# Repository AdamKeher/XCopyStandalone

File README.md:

# XCopy Standalone
An Arduino / Teensy based version of the Amiga XCopy application for copying floppy disks to and from ADF files. Built for the Teensy 3.2 using a custom PCB and an unmodified PC 3.5" floppy disk drive.

### Note
XCopy Standalone liberally uses floppy interface code taken from the excelent and generously open source ADF-Copy by Dominik Tonn. 
https://nickslabor.niteto.de/download/
Nicks software uses usb serial and a Java client or a MTP connection via usb to transfer data. XCopy Standalone focuses on a standalone unit using SD card storage and a LCD and / or web sockets interface for control.

### Thanks
Special thanks to Giants for all his help with this version including web interface graphics, documentation, suggestions etc.

## Device

## Status
This project is under heavy development and is in a state of flux with new hardware and software being actively worked on. The firmware version lives in `src/XCopy/XCopy.h`; this README describes v743.26.

## New Features - 09/2026

Since the 04/2023 release the device has grown a flux layer under the copier, a
second file system layer over the SD card, and a rebuilt web interface.

* **Disk Info** - a track analyser that describes what is on a disk rather than
  copying it. One pass per track, no retries, so a protected track with the wrong
  cylinder in its headers, a track with no sectors at all, or a disk with 84
  cylinders instead of 80 is the output rather than an error. Draws both surfaces
  as disks, a flux interval histogram per track, an angular track view you can
  point at, and the decoded sector under the pointer. Runs against the drive, or
  replays an SCP image through the same decoder.
* **Drive Toolkit** - a bench instrument for bringing up an unknown drive. Every
  interface line sampled with state, counts and rates; the safe outputs drivable
  one at a time, so a drive can be provoked into saying which fault it has; and a
  continuous head calibration read, after Amiga Test Kit's, that reports how many
  of the eleven sectors came back clean and whether the ones that did not came
  from the cylinder either side. Write data and write enable are deliberately not
  exposed.
* **SuperCard Pro flux images** - `readscp` captures a disk to an SCP file,
  streamed a block at a time because a single DD revolution is larger than the RAM
  on the whole part. A matching reader replays one back through the analyser.
* **Live USB flux streaming** - `live` hands the USB session to a host that does
  its own decoding, with non blocking in band seeking so the capture ring is still
  draining during a head move. Host side probe in `files/Tools/xcopylive_probe.py`.
* **ADF images as volumes** - mount ADF files as `ADF0:` and `ADF1:`, and the disk
  in the drive itself as `DF0:`, then use `dir`, `cat`, `cp`, `mkdir` and `rm`
  across the card and any mounted image. Mounts are read only unless asked
  otherwise. ADFlib upgraded to 0.10.7, with drivers rather than local edits.
* **New serial console** - a table driven interpreter with grouped help, per
  command options, tab completion and history, in place of the hand written parser.
* **Rebuilt web interface** - six tabs over one set of shared tokens and
  components, with the Disk Monitor histogram and the Disk Info analysis streamed
  to the browser as they are produced rather than gathered first.
* **Over the air updates** - firmware and web assets over Wi-Fi, no cable needed.
* **A name on the network** - the device calls itself `xcopy` to DHCP, to mDNS and
  to OTA.
* **Host side tests** - the `native` and `native_adf` environments run the file
  system and console tests off the board.

## New Features - 04/2023
* v0.19 PCB released with intergrated ESP8266 for WiFi
  * Moved to Kicad from Eagle
  * Changed SD Card to MicroSD reader
  * Added WiFi
  * Connected USB serial to Teensy USB serial
  * Moved TFT to cheap chinese Adafruit knock off, this has changed the pinout
    * https://www.aliexpress.com/item/4001144194129.html
    * USD $1.89!
  * Moved navigation stick to cheap chinese item from LCSC
  * Additional 3.3v power regulator to relieve Teensy's
  * Added larger electrolytic cap for floppy power
  * Switced to four layer board as they are cheap and provide better power / ground planes
* Project code moved from Arduino to ProjectIO with all libraries preinstalled
* New web interface
* Amiga module ripper
* Bootblock library / virus checker using brainfile format
* Web based disk monitor
* Network NTP time update
* Upload and download ADF files via web interface

## Features
* Software
  * Disk copy
    * Disk to SD Card
    * SD Card to Disk
    * Disk to Disk
    * Disk to Temporary Flash
    * Temporary Flash to Disk
  * Flux
    * Read a disk to a SuperCard Pro (SCP) flux image
    * Analyse a disk, or an SCP image, track by track
    * Flux interval histograms, per track and live during a copy
    * Stream a live drive to a host over USB for off board decoding
  * File systems
    * Amiga file system support for floppy disks and ADF files via ADFlib 0.10.7
    * Mount ADF images as `ADF0:` / `ADF1:`, and the disk in the drive as `DF0:`
    * List, print, copy, make and remove across the card and mounted images
  * Drive diagnostics
    * Every interface line sampled, with state, counts and rates
    * Individually drivable outputs for provoking a fault out of a drive
    * Continuous head calibration read with a live per cylinder tally
    * Drive speed from the index
  * Test disk
  * Format disk
  * Search a disk for case sensitive ascii text, or for tracker modules
  * Amiga module ripper
  * Bootblock library / virus checker using brainfile format
  * Serial command line, table driven, with tab completion and history
  * Interfaces
    * TFT LCD
    * USB Serial
    * HTML over WebSockets
  * Network
    * Over the air firmware and web asset updates
    * NTP time update and time zone
    * Announces itself as `xcopy` to DHCP, mDNS and OTA
  * Serial passthrough for programming onboard ESP8266
* Hardware
  * IDC 34 pin standard floppy drive cable interface
  * 1.8" ST7735R 128x160, 18bit color LCD
  * 5 way navigation joystick
  * Mono PAM8302 amplifier with adjustable Pot
    * Onboard mounted speaker
  * SD Card reader
  * 128MBit Flash Rom with built in ADF files
  * CR1220 battery backed realtime clock
  * ESP8266 for websockets driven interface
  * Single USB plug for serial and to power floppy and Teensy 3.2
  * Status LED's
  * Additional 3.3v power regulator
  * Gerbers, schematic and pcb layout files available 

# PCB

# Web Interface

Six tabs over one WebSocket connection to the ESP8266. The footer carries the
signal strength, the link state and what the device is doing, on every tab.

### Disk Copy

Every copy path in one place - between the drive, the SD card, the onboard flash,
and an ADF or SCP file on the card - over a live track map of both surfaces and a
rolling flux view of the track being read.

### Disk Monitor

A sector at a time: the decoded header, a hex dump, an ascii dump in either the
browser font or the Amiga one, and the track's flux histogram. Below them a block
scan of the whole disk, with ascii and tracker module searches, and blocks that
can be selected and written out to the card.

### Disk Info

The analyser. Both surfaces drawn as disks with every sector coloured by what was
found there, a status panel for the selected track, an angular track view of the
raw cell stream against the sectors decoded out of it, the flux histogram, and the
decoded sector under the pointer.

### Drive Toolkit

The drive itself rather than the disk in it. Sampled interface lines down the
left, the calibration read across the top, and a session tally that accumulates
per cylinder and head - so an intermittent read shows up as intermittent rather
than as one bad pass.

### SD Card

The contents of the card, with upload and download.

### Log

The serial console in the browser - the same interpreter, the same commands and
the same output as the USB port.

# Build Environment Notes:

## VSCode Plugins:
1. PlatoformIO with Teensy & ESP8266 board 
2. Todo+ v4.18.4 by Fabio Spampinato

* Xcopy.h contains PCBVERSION define to target firmware builds to different PCB versions

## ESP8266 Build Notes:
1. Select the `d1_mini` environment (both boards are environments of this one project)
2. Plugin XCopyStandalone device and select "Debugging >> ESP >> ESP Programming Mode"
3. Set serial port to the Teensy port, the device will passthrough serial data to the ESP8266 program
4. Upload code, then upload the web assets with the `d1_mini` "Build Filesystem Image" and "Upload Filesystem Image" tasks

### Over the air

Once the ESP is on your network it can be updated over Wi-Fi instead, using the
`d1_mini_ota` environment - both the firmware and the web assets:

```shell
pio run -e d1_mini_ota -t upload      # firmware
pio run -e d1_mini_ota -t uploadfs    # web interface
pio run -e d1_mini_ota -t uploadall   # both, firmware first
```

`uploadall` is a task of this project rather than of PlatformIO, and it waits
between the two because each upload reboots the ESP.

Use `uploadfs` for the web assets, not `uploadfsota`. The platform decides
whether espota is offering a sketch or a filesystem image by matching the target
name exactly, and `uploadfsota` misses that test - so the image goes over as a
sketch, is measured against the 1MB sketch region instead of its own 2MB
partition, and is refused with `ERROR[4]: Not Enough Space`. `scripts/
espota_fs_flag.py` puts the missing flag back, so both targets now work.

The device calls itself `xcopy` to the DHCP server, to mDNS and to OTA, so it is
reachable by whichever name your network gives it. `upload_port` in
`platformio.ini` is set to `xcopy.lab` - change it to `xcopy.local` to go via
mDNS instead, or to a bare IP address if neither resolves from your machine.

The serial passthrough above is unchanged and remains the way back in if an
update ever leaves the ESP unable to join a network.
5. Select "Debugging >> ESP >> Reset ESP"
6. Open a serial terminal
7. Connect to your wireless access point using the connect command
```shell
>> connect SSIDName Password
```
8. Type the following commands to confirm you have connected
```shell
>> status
WiFi Status: Connected
-----
Mode: STA
PHY mode: N
Channel: 10
AP id: 0
Status: 5
Auto connect: 1
SSID (6): SSIDName
Passphrase (12): Password
BSSID set: 0
>> ip
192.168.X.XX
>> ssid
SSIDName
>>
```

## Project layout

Both firmwares are environments of a single PlatformIO project, so the IDE lists
them in one Project Tasks tree and `pio run` with no arguments builds the pair.

| | |
|---|---|
| `src/` | Teensy 3.2 firmware, built by the `teensy31` environment |
| `src/esp8266/` | ESP8266 firmware, built by the `d1_mini` environment |
| `esp8266/data/` | web interface, uploaded to the ESP as a LittleFS image |
| `shared/` | the Teensy to ESP link contract, compiled into both |
| `lib/` | libraries for both; `esp8266/lib/` holds the ESP only ones |

Both boards are environments of the one project: `teensy31`, `d1_mini`, and
`d1_mini_ota` for updating the ESP over Wi-Fi. Two more, `native` and
`native_adf`, build nothing for a board and exist to run the console and file
system tests on the host.

Neither firmware is a `.ino` sketch: PlatformIO only converts a sketch sitting at
the top of the source directory, and with two source trees neither one can be.

## How to build PlatformIO based project

1. [Install PlatformIO Core](http://docs.platformio.org/page/core.html)
2. Download [development platform with examples](https://github.com/platformio/platform-teensy/archive/develop.zip)
3. Open the project
4. Pick the environment you want - `teensy31` or `d1_mini` - or build both at once
5. Select 'PlatformIO:Build'
6. Select 'PlatformIO:Upload'

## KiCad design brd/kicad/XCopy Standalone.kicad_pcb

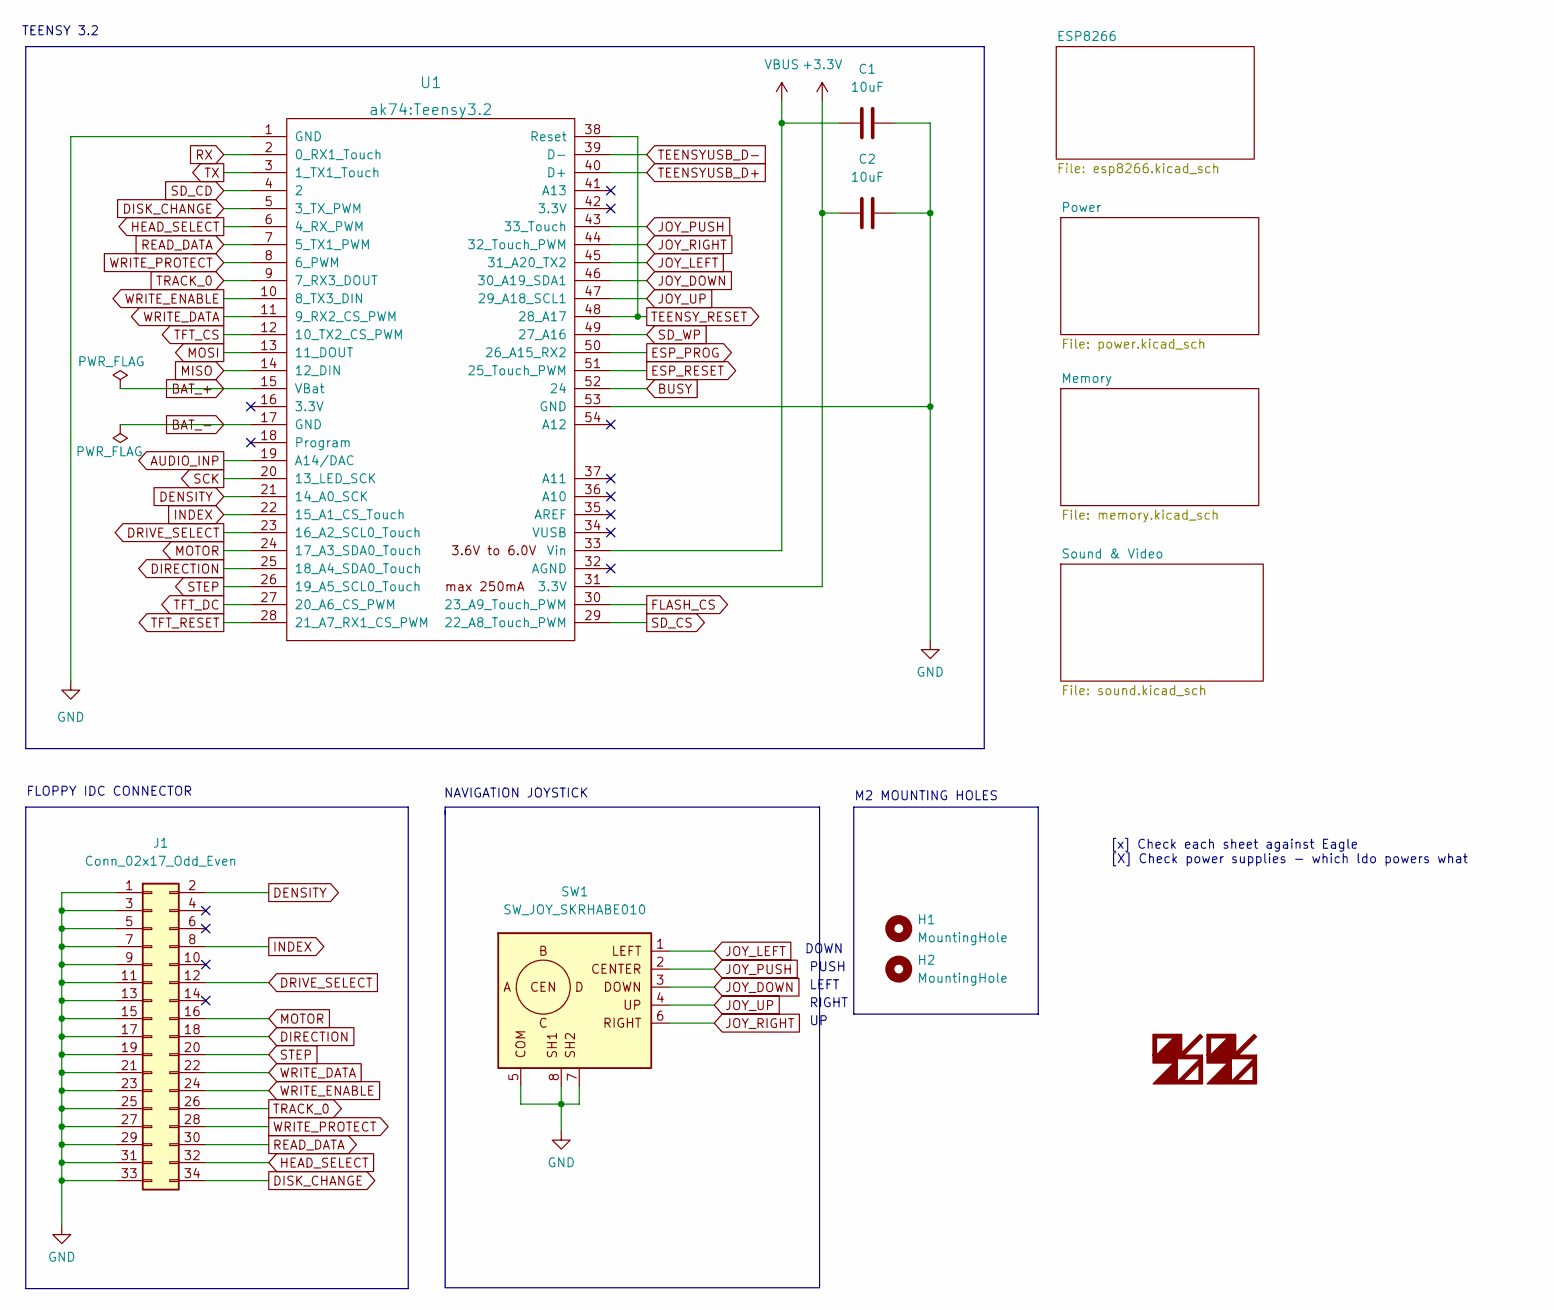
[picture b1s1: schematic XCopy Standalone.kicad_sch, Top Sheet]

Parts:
C1, C2: 10uF; C_0603_1608Metric_Pad1.08x0.95mm_HandSolder
H1, H2: MountingHole; MountingHole_2.2mm_M2
J1: Conn_02x17_Odd_Even; IDC-Header_2x17_P2.54mm_Horizontal_FLOPPY
SW1: SW_JOY_SKRHABE010; Switches_ALPS-SKRHAAE010; LCSC C139794
U1: ak74:Teensy3.2; Teensy30_31_32_All_Pins

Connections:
+3.3V: C2.2, U1.31 (3.3V); also elsewhere on the board
AUDIO_INP: U1.19 (A14/DAC); also elsewhere on the board
BAT_+: U1.15 (VBat); also elsewhere on the board
BAT_-: U1.17 (GND); also elsewhere on the board
BUSY: U1.52 (24); also elsewhere on the board
DENSITY: J1.2, U1.21 (14_A0_SCK)
DIRECTION: J1.18, U1.25 (18_A4_SDA0_Touch)
DISK_CHANGE: J1.34, U1.5 (3_TX_PWM)
DRIVE_SELECT: J1.12, U1.23 (16_A2_SCL0_Touch)
ESP_PROG: U1.50 (26_A15_RX2); also elsewhere on the board
ESP_RESET: U1.51 (25_Touch_PWM); also elsewhere on the board
FLASH_CS: U1.30 (23_A9_Touch_PWM); also elsewhere on the board
GND: C1.1, C2.1, J1.1, J1.3, J1.5, J1.7, J1.9, J1.11, J1.13, J1.15, J1.17, J1.19, J1.21, J1.23, J1.25, J1.27, J1.29, J1.31, J1.33, SW1.5 (COM), SW1.7 (SH2), SW1.8 (SH1), U1.1 (GND), U1.53 (GND); also elsewhere on the board
HEAD_SELECT: J1.32, U1.6 (4_RX_PWM)
INDEX: J1.8, U1.22 (15_A1_CS_Touch)
JOY_DOWN: SW1.3 (C), U1.46 (30_A19_SDA1)
JOY_LEFT: SW1.1 (A), U1.45 (31_A20_TX2); also elsewhere on the board
JOY_PUSH: SW1.2 (Center), U1.43 (33_Touch)
JOY_RIGHT: SW1.6 (D), U1.44 (32_Touch_PWM)
JOY_UP: SW1.4 (B), U1.47 (29_A18_SCL1)
MISO: U1.14 (12_DIN); also elsewhere on the board
MOSI: U1.13 (11_DOUT); also elsewhere on the board
MOTOR: J1.16, U1.24 (17_A3_SDA0_Touch)
READ_DATA: J1.30, U1.7 (5_TX1_PWM)
RX: U1.2 (0_RX1_Touch); also elsewhere on the board
SCK: U1.20 (13_LED_SCK); also elsewhere on the board
SD_CD: U1.4 (2); also elsewhere on the board
SD_CS: U1.29 (22_A8_Touch_PWM); also elsewhere on the board
SD_WP: U1.49 (27_A16); also elsewhere on the board
STEP: J1.20, U1.26 (19_A5_SCL0_Touch)
TEENSYUSB_D+: U1.40 (D+); also elsewhere on the board
TEENSYUSB_D-: U1.39 (D-); also elsewhere on the board
TEENSY_RESET: U1.38 (Reset), U1.48 (28_A17); also elsewhere on the board
TFT_CS: U1.12 (10_TX2_CS_PWM); also elsewhere on the board
TFT_DC: U1.27 (20_A6_CS_PWM); also elsewhere on the board
TFT_RESET: U1.28 (21_A7_RX1_CS_PWM); also elsewhere on the board
TRACK_0: J1.26, U1.9 (7_RX3_DOUT)
TX: U1.3 (1_TX1_Touch); also elsewhere on the board
VBUS: C1.2, U1.33 (Vin); also elsewhere on the board
WRITE_DATA: J1.22, U1.11 (9_RX2_CS_PWM)
WRITE_ENABLE: J1.24, U1.10 (8_TX3_DIN)
WRITE_PROTECT: J1.28, U1.8 (6_PWM)

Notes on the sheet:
DOWN
NAVIGATION JOYSTICK
TEENSY 3.2
[x] Check each sheet against Eagle [X] Check power supplies - which ldo powers what
M2 MOUNTING HOLES
FLOPPY IDC CONNECTOR
LEFT
RIGHT
PUSH

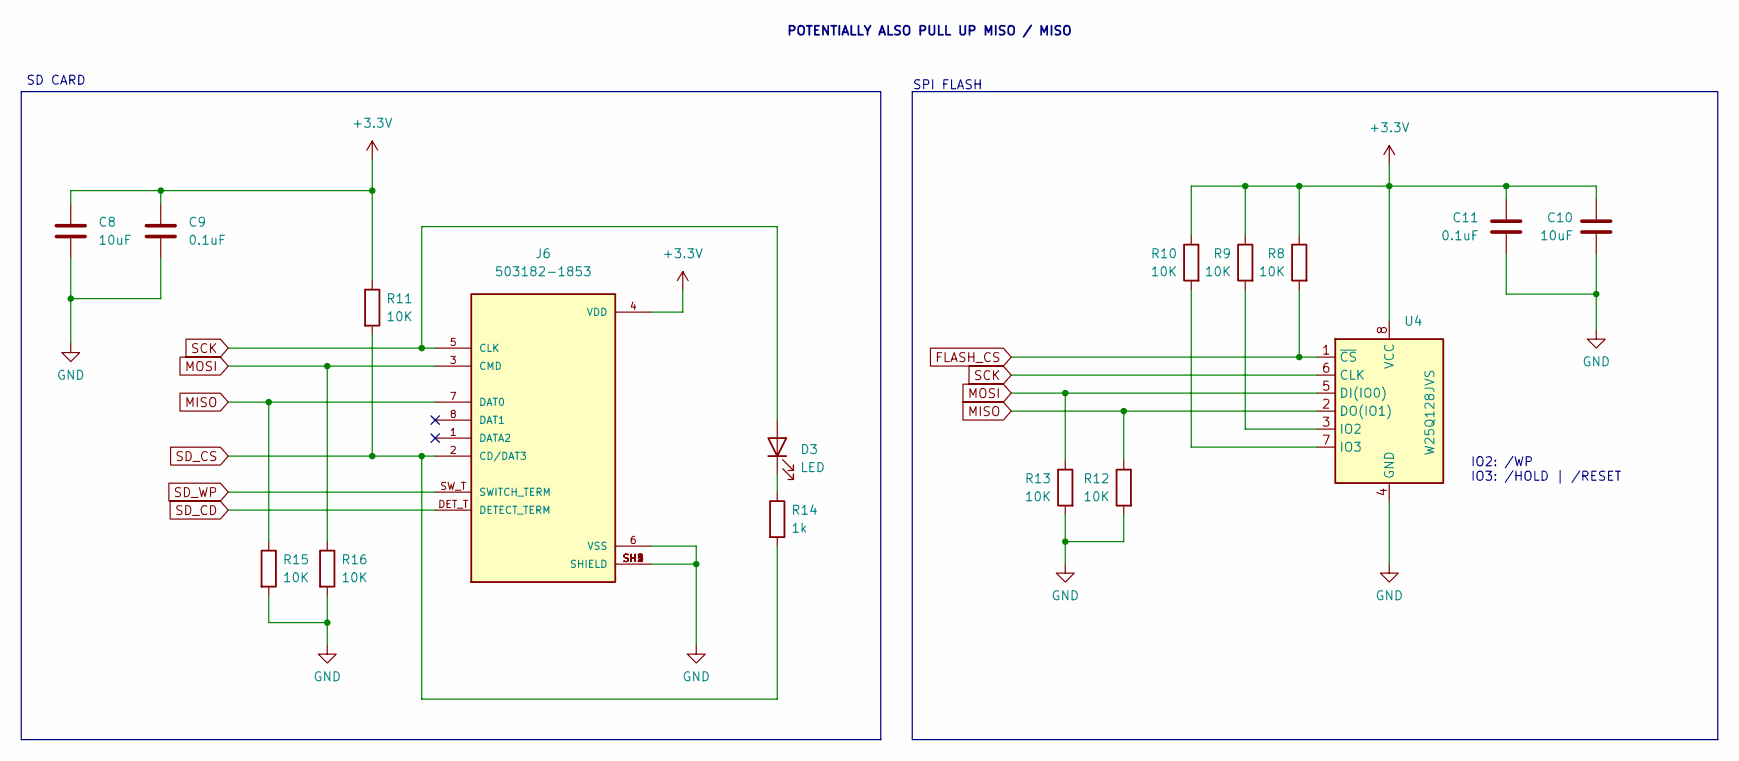
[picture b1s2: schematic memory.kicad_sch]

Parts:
C8, C10: 10uF; C_0603_1608Metric_Pad1.08x0.95mm_HandSolder
C9, C11: 0.1uF; C_0603_1608Metric_Pad1.08x0.95mm_HandSolder
D3: LED; LED_0603_1608Metric_Pad1.05x0.95mm_HandSolder
J6: 503182-1853; MOLEX_503182-1853-2; PARTREV G; LCSC C266617
R8, R9, R10, R11, R12, R13, R15, R16: 10K; R_0603_1608Metric_Pad0.98x0.95mm_HandSolder
R14: 1k; R_0603_1608Metric_Pad0.98x0.95mm_HandSolder
U4: W25Q128JVS; SOIC-8_5.23x5.23mm_P1.27mm; LCSC C571265

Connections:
+3.3V: C8.1, C9.1, C10.1, C11.1, J6.4 (VDD), R8.1, R9.1, R10.1, R11.1, U4.8 (VCC); also elsewhere on the board
FLASH_CS: R8.2, U4.1 (~CS); also elsewhere on the board
GND: C8.2, C9.2, C10.2, C11.2, J6.6 (VSS), J6.SH1 (SHIELD), J6.SH2 (SHIELD), J6.SH3 (SHIELD), J6.SH4 (SHIELD), J6.SH5 (SHIELD), R12.2, R13.2, R15.2, R16.2, U4.4 (GND); also elsewhere on the board
MISO: J6.7 (DAT0), R12.1, R15.1, U4.2 (DO(IO1)); also elsewhere on the board
MOSI: J6.3 (CMD), R13.1, R16.1, U4.5 (DI(IO0)); also elsewhere on the board
unnamed: D3.1 (K), R14.1
unnamed: R9.2, U4.3 (IO2)
unnamed: R10.2, U4.7 (IO3)
SCK: D3.2 (A), J6.5 (CLK), U4.6 (CLK); also elsewhere on the board
SD_CD: J6.DET_T (DETECT_TERM); also elsewhere on the board
SD_CS: J6.2 (CD/DAT3), R11.2, R14.2; also elsewhere on the board
SD_WP: J6.SW_T (SWITCH_TERM); also elsewhere on the board

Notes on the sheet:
SD CARD
IO2: /WP IO3: /HOLD | /RESET
POTENTIALLY ALSO PULL UP MISO / MISO
SPI FLASH

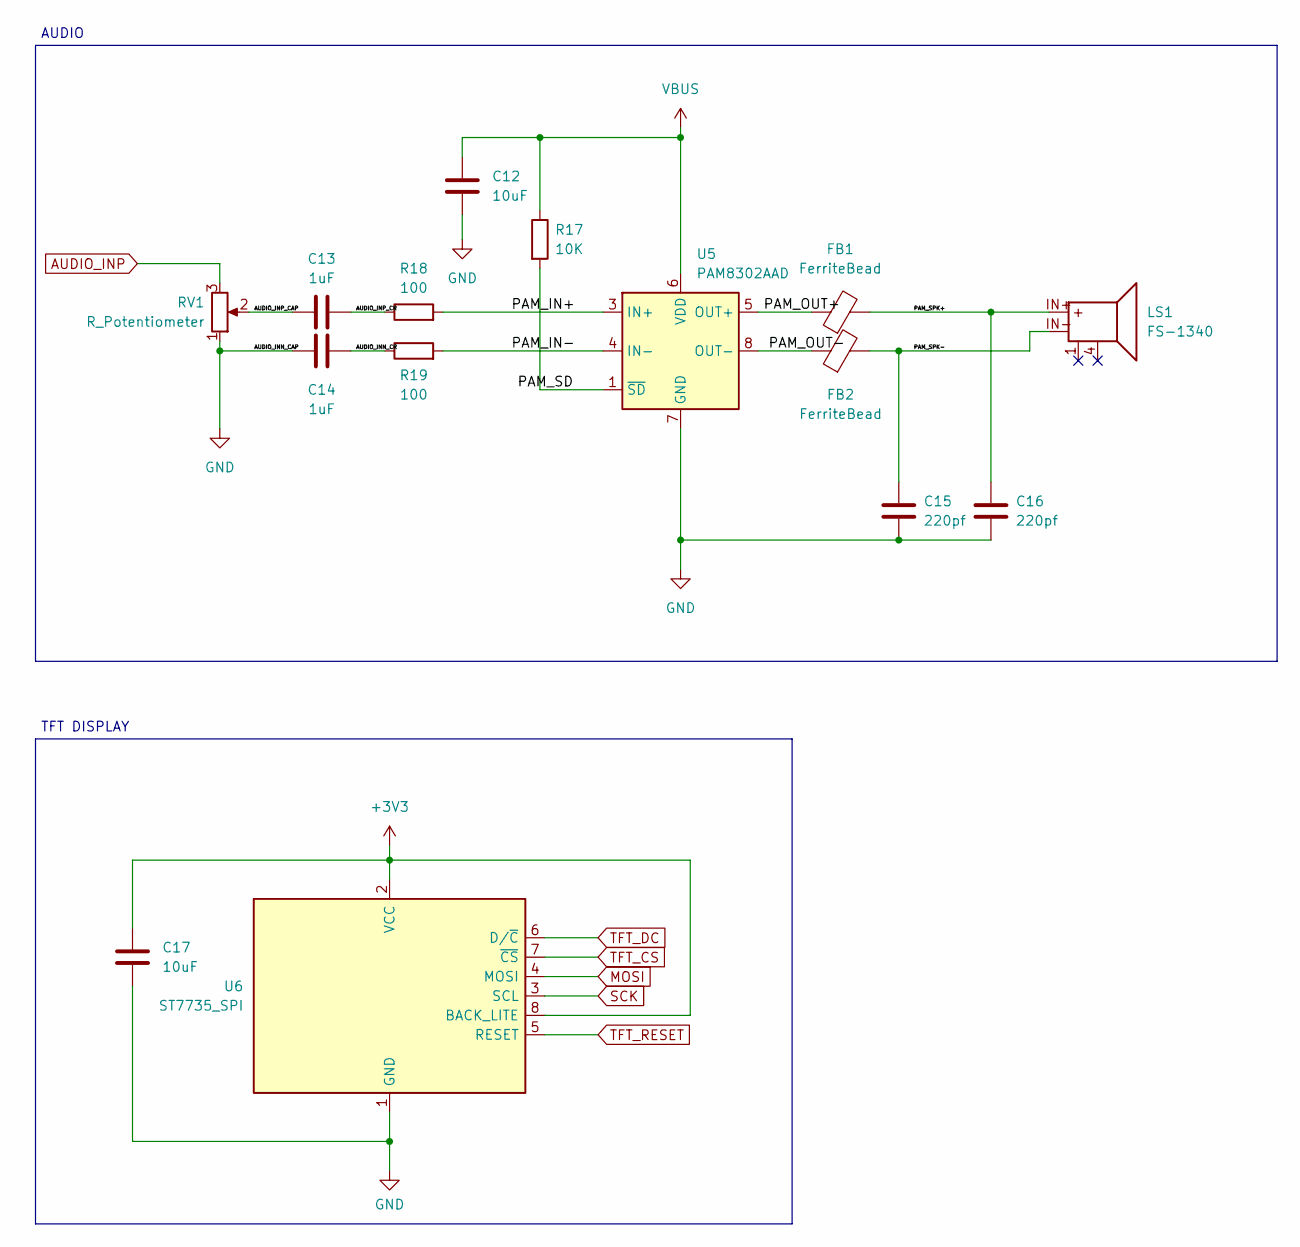
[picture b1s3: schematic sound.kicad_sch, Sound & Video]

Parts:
C12, C17: 10uF; C_0603_1608Metric_Pad1.08x0.95mm_HandSolder
C13, C14: 1uF; C_0603_1608Metric_Pad1.08x0.95mm_HandSolder
C15, C16: 220pf; C_0603_1608Metric_Pad1.08x0.95mm_HandSolder
FB1, FB2: FerriteBead; R_0805_2012Metric_Pad1.20x1.40mm_HandSolder
LS1: FS-1340; SPK_FUET_FS-1340; LCSC C482342
R17: 10K; R_0603_1608Metric_Pad0.98x0.95mm_HandSolder
R18, R19: 100; R_0603_1608Metric_Pad0.98x0.95mm_HandSolder
RV1: R_Potentiometer; Potentiometer_Bourns_TC33X-2; LCSC C719176
U5: PAM8302AAD; SOP-8_3.9x4.9mm_P1.27mm; LCSC C112137
U6: ST7735_SPI; 1.8in_TFT_ST7735

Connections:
+3V3: C17.2, U6.2 (VCC), U6.8 (BACK_LITE); also elsewhere on the board
/Sound & Video/AUDIO_INN_CR: C14.1, R19.1
/Sound & Video/AUDIO_INP_CAP: C13.1, RV1.2
/Sound & Video/AUDIO_INP_CR: C13.2, R18.1
/Sound & Video/PAM_IN+: R18.2, U5.3 (IN+)
/Sound & Video/PAM_IN-: R19.2, U5.4 (IN-)
/Sound & Video/PAM_OUT+: FB1.1, U5.5 (OUT+)
/Sound & Video/PAM_OUT-: FB2.1, U5.8 (OUT-)
/Sound & Video/PAM_SD: R17.2, U5.1 (~SD)
/Sound & Video/PAM_SPK+: C16.2, FB1.2, LS1.IN+
/Sound & Video/PAM_SPK-: C15.2, FB2.2, LS1.IN-
AUDIO_INP: RV1.3; also elsewhere on the board
GND: C12.2, C14.2, C15.1, C16.1, C17.1, RV1.1, U5.7 (GND), U6.1 (GND); also elsewhere on the board
MOSI: U6.4 (MOSI); also elsewhere on the board
SCK: U6.3 (SCL); also elsewhere on the board
TFT_CS: U6.7 (~CS); also elsewhere on the board
TFT_DC: U6.6 (D/~C); also elsewhere on the board
TFT_RESET: U6.5 (RESET); also elsewhere on the board
VBUS: C12.1, R17.1, U5.6 (VDD); also elsewhere on the board

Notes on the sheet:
AUDIO
TFT DISPLAY

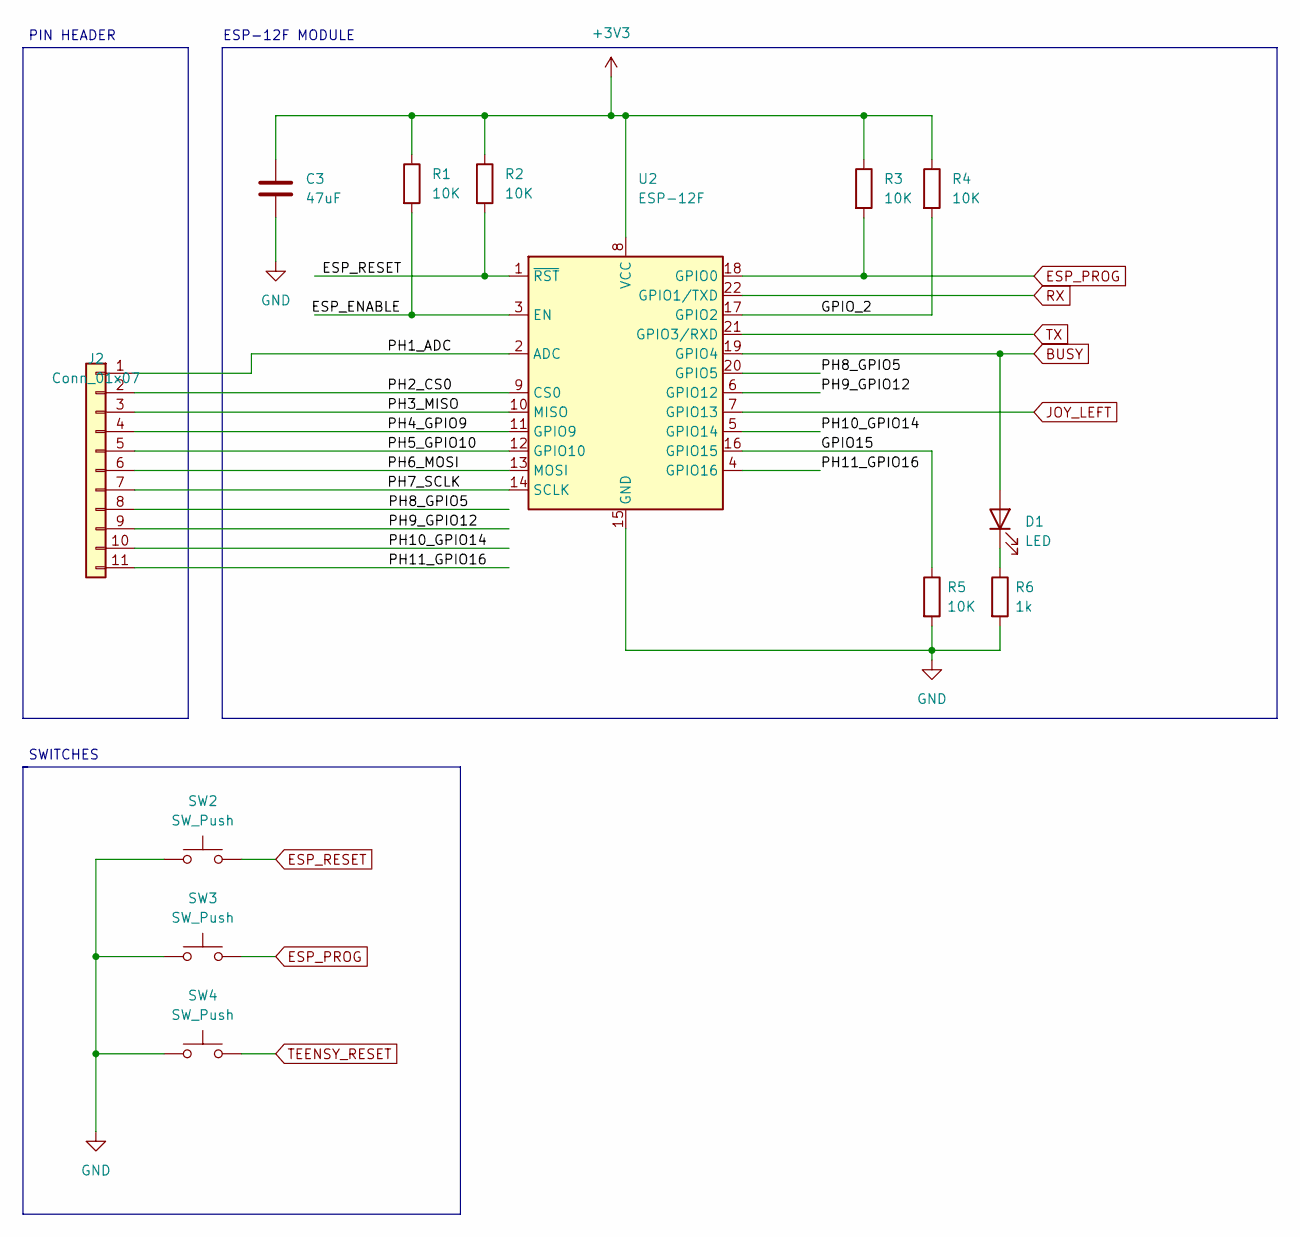
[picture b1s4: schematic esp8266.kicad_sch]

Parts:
C3: 47uF; C_0805_2012Metric_Pad1.18x1.45mm_HandSolder
D1: LED; LED_0603_1608Metric_Pad1.05x0.95mm_HandSolder
J2: Conn_01x07; PinHeader_1x11_P2.54mm_Vertical
R1, R2, R3, R4, R5: 10K; R_0603_1608Metric_Pad0.98x0.95mm_HandSolder
R6: 1k; R_0603_1608Metric_Pad0.98x0.95mm_HandSolder
SW2, SW3, SW4: SW_Push; SW_SKSCLDE010; LCSC C115362
U2: ESP-12F; ESP-12E

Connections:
+3V3: C3.1, R1.1, R2.1, R3.1, R4.1, U2.8 (VCC); also elsewhere on the board
/ESP8266/ESP_ENABLE: R1.2, U2.3 (EN)
/ESP8266/GPIO15: R5.1, U2.16 (GPIO15)
/ESP8266/GPIO_2: R4.2, U2.17 (GPIO2)
/ESP8266/PH1_ADC: J2.1, U2.2 (ADC)
/ESP8266/PH2_CS0: J2.2, U2.9 (CS0)
/ESP8266/PH3_MISO: J2.3, U2.10 (MISO)
/ESP8266/PH4_GPIO9: J2.4, U2.11 (GPIO9)
/ESP8266/PH5_GPIO10: J2.5, U2.12 (GPIO10)
/ESP8266/PH6_MOSI: J2.6, U2.13 (MOSI)
/ESP8266/PH7_SCLK: J2.7, U2.14 (SCLK)
/ESP8266/PH8_GPIO5: J2.8, U2.20 (GPIO5)
/ESP8266/PH9_GPIO12: J2.9, U2.6 (GPIO12)
/ESP8266/PH10_GPIO14: J2.10, U2.5 (GPIO14)
/ESP8266/PH11_GPIO16: J2.11, U2.4 (GPIO16)
BUSY: D1.2 (A), U2.19 (GPIO4); also elsewhere on the board
ESP_PROG: R3.2, SW3.2, U2.18 (GPIO0); also elsewhere on the board
ESP_RESET: R2.2, SW2.2, U2.1 (~RST); also elsewhere on the board
GND: C3.2, R5.2, R6.2, SW2.1, SW3.1, SW4.1, U2.15 (GND); also elsewhere on the board
JOY_LEFT: U2.7 (GPIO13); also elsewhere on the board
unnamed: D1.1 (K), R6.1
RX: U2.22 (GPIO1/TXD); also elsewhere on the board
TEENSY_RESET: SW4.2; also elsewhere on the board
TX: U2.21 (GPIO3/RXD); also elsewhere on the board

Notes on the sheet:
ESP-12F MODULE
PIN HEADER
SWITCHES

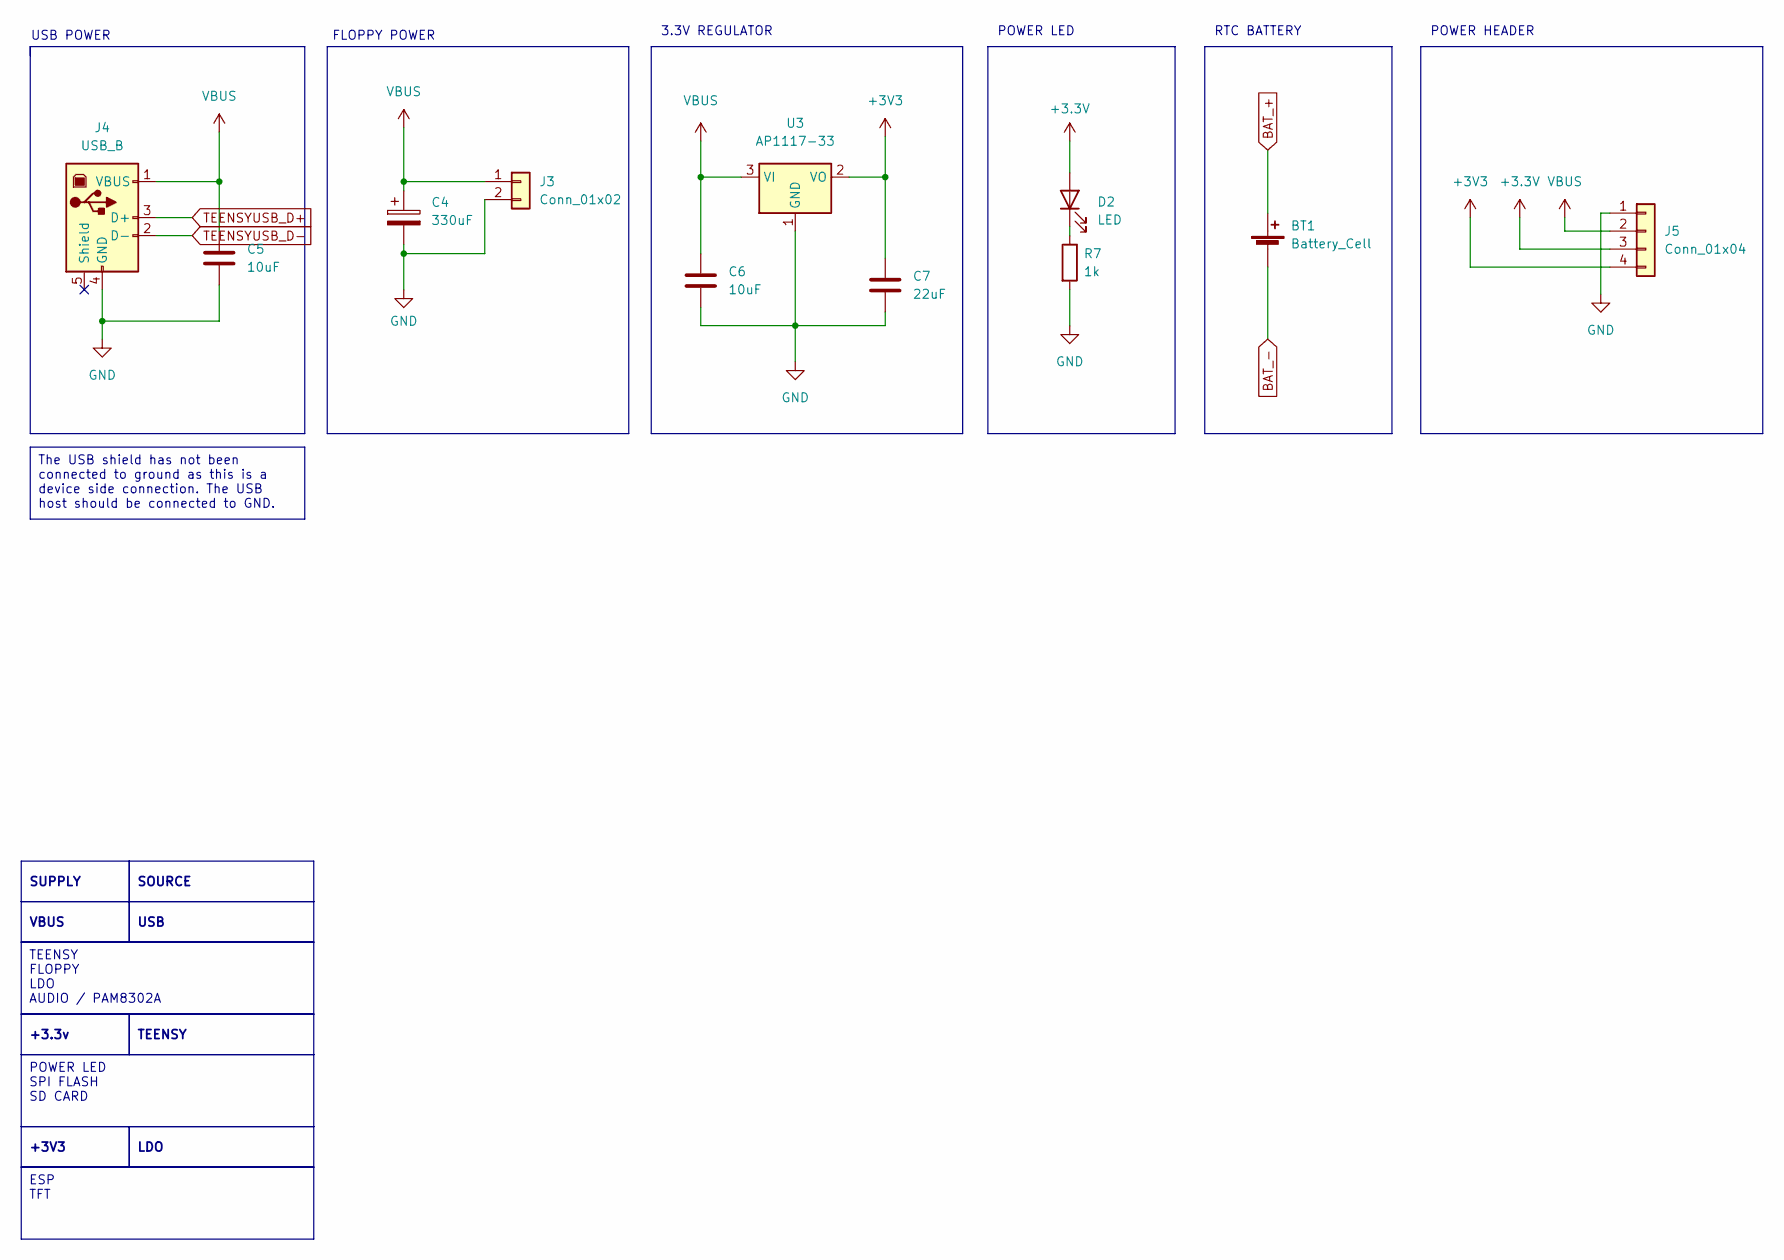
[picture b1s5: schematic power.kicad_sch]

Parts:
BT1: Battery_Cell; keystone-PN1056TR; LCSC C964750
C4: 330uF; CP_Elec_6.3x5.8; LCSC C286137
C5, C6: 10uF; C_0603_1608Metric_Pad1.08x0.95mm_HandSolder
C7: 22uF; C_0603_1608Metric_Pad1.08x0.95mm_HandSolder
D2: LED; LED_0603_1608Metric_Pad1.05x0.95mm_HandSolder
J3: Conn_01x02; PinHeader_1x02_P2.54mm_Vertical
J4: USB_B; USB_B_OST_USB_Horizontal-Jing-Extension-111A1010D10200; LCSC C46392
J5: Conn_01x04; PinHeader_2x02_P2.54mm_Vertical
R7: 1k; R_0603_1608Metric_Pad0.98x0.95mm_HandSolder
U3: AP1117-33; SOT-223-3_TabPin2; LCSC C347222

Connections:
+3.3V: D2.2 (A), J5.3; also elsewhere on the board
+3V3: C7.1, J5.4, U3.2 (VO); also elsewhere on the board
BAT_+: BT1.1 (+); also elsewhere on the board
BAT_-: BT1.2 (-); also elsewhere on the board
GND: C4.2, C5.2, C6.2, C7.2, J3.2, J4.4 (GND), J5.1, R7.2, U3.1 (GND); also elsewhere on the board
unnamed: D2.1 (K), R7.1
TEENSYUSB_D+: J4.3 (D+); also elsewhere on the board
TEENSYUSB_D-: J4.2 (D-); also elsewhere on the board
VBUS: C4.1, C5.1, C6.1, J3.1, J4.1 (VBUS), J5.2, U3.3 (VI); also elsewhere on the board

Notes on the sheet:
POWER LED SPI FLASH SD CARD
TEENSY
ESP TFT
TEENSY FLOPPY LDO AUDIO / PAM8302A
USB
The USB shield has not been connected to ground as this is a device side connection. The USB host should be connected to GND.
LDO
SUPPLY
+3V3
VBUS
SOURCE
+3.3v
3.3V REGULATOR
RTC BATTERY
POWER LED
FLOPPY POWER
POWER HEADER
USB POWER

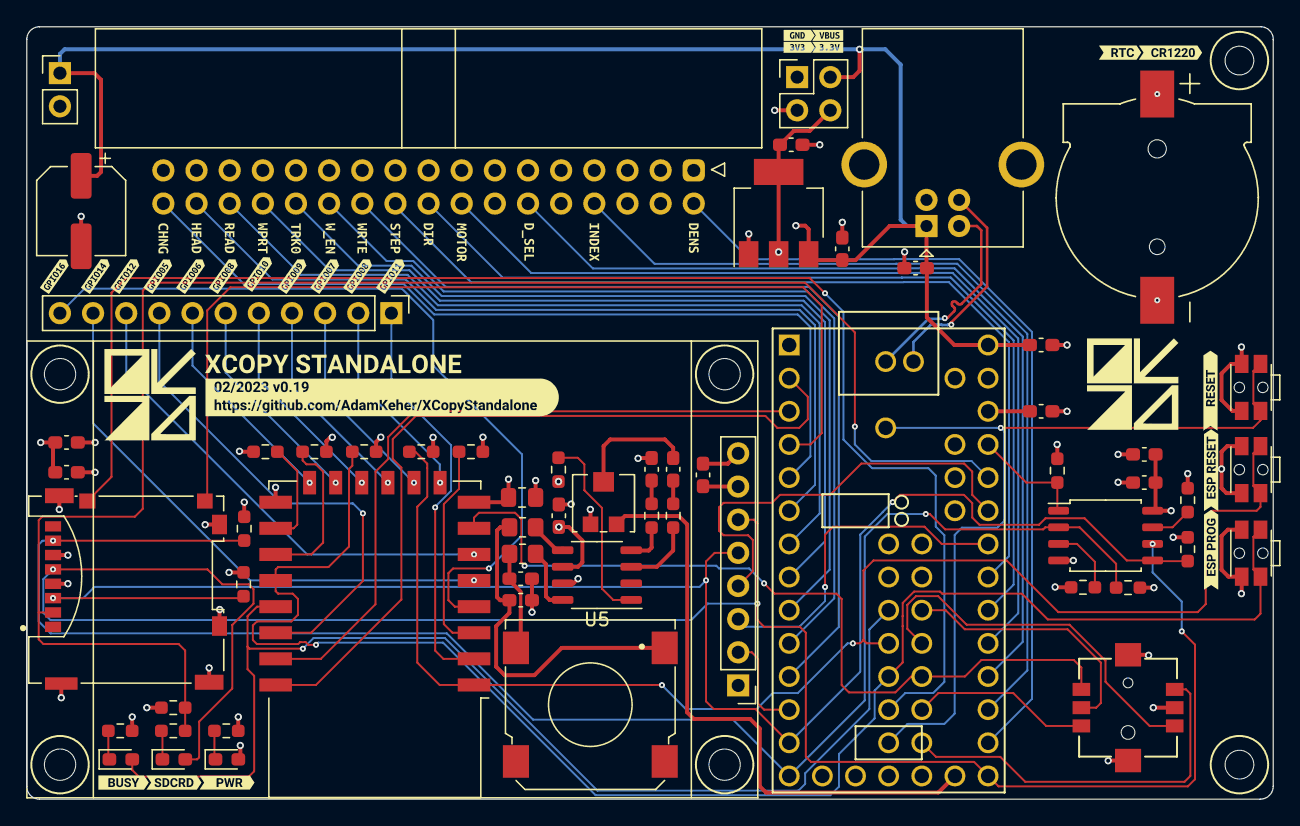
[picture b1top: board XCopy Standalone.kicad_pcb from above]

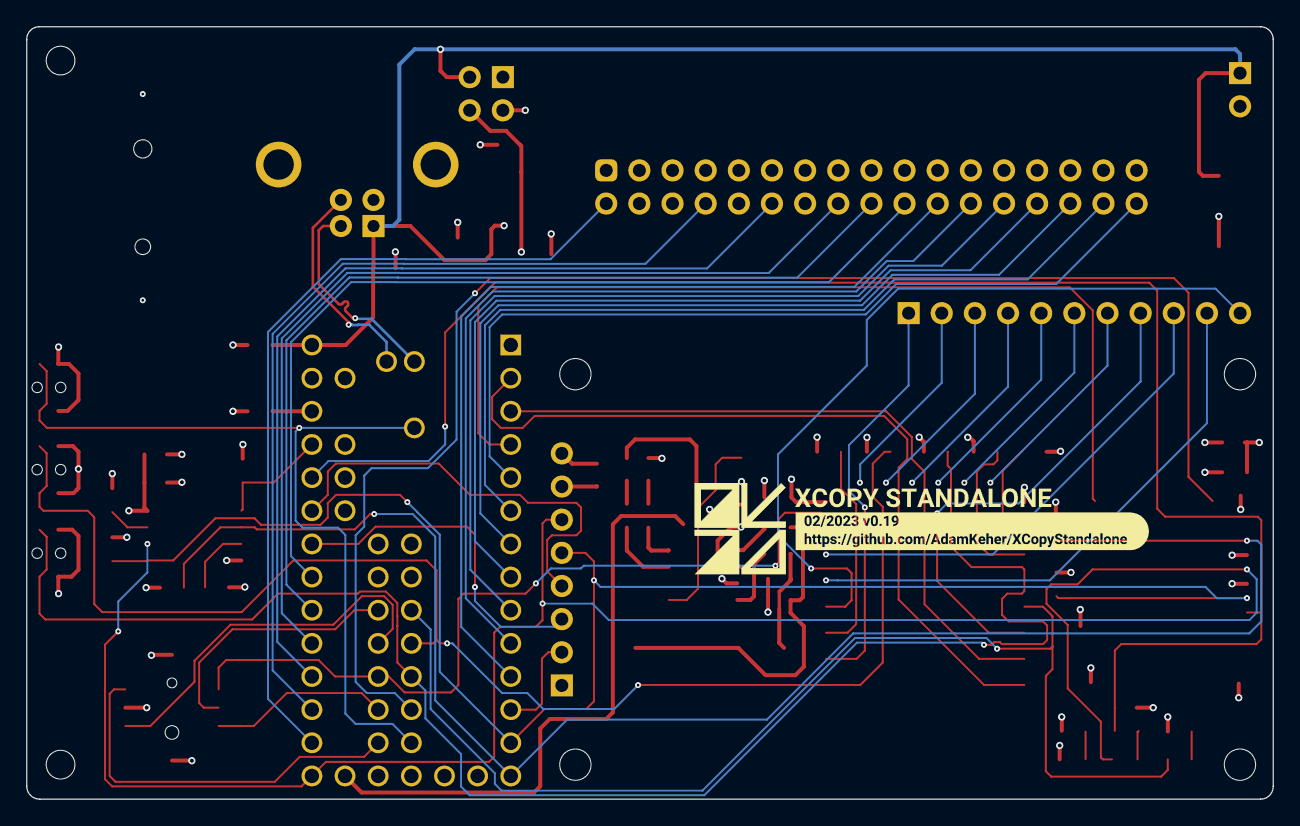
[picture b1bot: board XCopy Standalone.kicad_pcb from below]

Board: 4 copper layers, 95.5 x 59.2 mm, 102 parts (2 on the bottom side), 72 nets.

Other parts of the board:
kibuzzard-63E64A01: G***; kibuzzard-63E64A01
kibuzzard-63E64B6F: G***; kibuzzard-63E64B6F
kibuzzard-63E64BAD: G***; kibuzzard-63E64BAD
kibuzzard-63E65A6E: G***; kibuzzard-63E65A6E
kibuzzard-63E65E35, kibuzzard-63E65E35#2: G***; kibuzzard-63E65E35
kibuzzard-63E65F2C: G***; kibuzzard-63E65F2C
kibuzzard-63E65F17: G***; kibuzzard-63E65F17
kibuzzard-63E78C9C: G***; kibuzzard-63E78C9C
kibuzzard-63E78C36: G***; kibuzzard-63E78C36
kibuzzard-63E78C45: G***; kibuzzard-63E78C45
kibuzzard-63E78C77: G***; kibuzzard-63E78C77
kibuzzard-63E648B8, kibuzzard-63E648B8#2: G***; kibuzzard-63E648B8
kibuzzard-63E649A5: G***; kibuzzard-63E649A5
kibuzzard-63E649C1: G***; kibuzzard-63E649C1
kibuzzard-63E649E9: G***; kibuzzard-63E649E9
kibuzzard-63E650D0: G***; kibuzzard-63E650D0
kibuzzard-63E650FB: G***; kibuzzard-63E650FB
kibuzzard-63E651BF: G***; kibuzzard-63E651BF
kibuzzard-63E652DF, kibuzzard-63E652DF#2: G***; kibuzzard-63E652DF
kibuzzard-63E655A7: G***; kibuzzard-63E655A7
kibuzzard-63E6473B: G***; kibuzzard-63E6473B
kibuzzard-63E6479F: G***; kibuzzard-63E6479F
kibuzzard-63E6490B: G***; kibuzzard-63E6490B
kibuzzard-63E6512D: G***; kibuzzard-63E6512D
kibuzzard-63E6513B: G***; kibuzzard-63E6513B
kibuzzard-63E6514F: G***; kibuzzard-63E6514F
kibuzzard-63E6515C: G***; kibuzzard-63E6515C
kibuzzard-63E6582B: G***; kibuzzard-63E6582B
kibuzzard-63E65082: G***; kibuzzard-63E65082
kibuzzard-63E65107: G***; kibuzzard-63E65107
kibuzzard-63E65113: G***; kibuzzard-63E65113
kibuzzard-63E65145: G***; kibuzzard-63E65145
kibuzzard-63E65580: G***; kibuzzard-63E65580
kibuzzard-63E65598: G***; kibuzzard-63E65598
kibuzzard-63E65800: G***; kibuzzard-63E65800
kibuzzard-63E65845: G***; kibuzzard-63E65845
kibuzzard-63E65952: G***; kibuzzard-63E65952

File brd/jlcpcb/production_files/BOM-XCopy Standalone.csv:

Comment,Designator,Footprint,LCSC,QTY
FerriteBead,"FB1,FB2",R_0805_2012Metric_Pad1.20x1.40mm_HandSolder,C1015,2
PAM8302AAD,U5,SOP-8_3.9x4.9mm_P1.27mm,C112137,1
SW_Push,"SW2,SW3,SW4",SW_SKSCLDE010,C115362,3
SW_JOY_SKRHABE010,SW1,Switches_ALPS-SKRHAAE010,C139794,1
0.1uF,"C11,C9",C_0603_1608Metric_Pad1.08x0.95mm_HandSolder,C14663,2
1uF,"C13,C14",C_0603_1608Metric_Pad1.08x0.95mm_HandSolder,C15849,2
220pf,"C15,C16",C_0603_1608Metric_Pad1.08x0.95mm_HandSolder,C1603,2
47uF,C3,C_0805_2012Metric_Pad1.18x1.45mm_HandSolder,C16780,1
10uF,"C1,C10,C12,C17,C2,C5,C6,C8",C_0603_1608Metric_Pad1.08x0.95mm_HandSolder,C19702,8
1k,"R14,R6,R7",R_0603_1608Metric_Pad0.98x0.95mm_HandSolder,C21190,3
100,"R18,R19",R_0603_1608Metric_Pad0.98x0.95mm_HandSolder,C22775,2
10K,"R1,R10,R11,R12,R13,R15,R16,R17,R2,R3,R4,R5,R8,R9",R_0603_1608Metric_Pad0.98x0.95mm_HandSolder,C25804,14
503182-1853,J6,MOLEX_503182-1853-2,C266617,1
330uF,C4,CP_Elec_6.3x5.8,C286137,1
AP1117-33,U3,SOT-223-3_TabPin2,C347222,1
USB_B,J4,USB_B_OST_USB_Horizontal-Jing-Extension-111A1010D10200,C46392,1
FS-1340,LS1,SPK_FUET_FS-1340,C482342,1
W25Q128JVS,U4,SOIC-8_5.23x5.23mm_P1.27mm,C571265,1
22uF,C7,C_0603_1608Metric_Pad1.08x0.95mm_HandSolder,C59461,1
R_Potentiometer,RV1,Potentiometer_Bourns_TC33X-2,C719176,1
LED,D3,LED_0603_1608Metric_Pad1.05x0.95mm_HandSolder,C72038,1
LED,D1,LED_0603_1608Metric_Pad1.05x0.95mm_HandSolder,C72039,1
LED,D2,LED_0603_1608Metric_Pad1.05x0.95mm_HandSolder,C72043,1
ESP-12F,U2,ESP-12E,C82891,1
Battery_Cell,BT1,keystone-PN1056TR,C964750,1
ST7735_SPI,U6,1.8in_TFT_ST7735,,1
Conn_02x17_Odd_Even,J1,IDC-Header_2x17_P2.54mm_Horizontal_FLOPPY,,1
Conn_01x02,J3,PinHeader_1x02_P2.54mm_Vertical,,1
ak74:Teensy3.2,U1,Teensy30_31_32_All_Pins,,1
MountingHole,H1,MountingHole_2.2mm_M2,,1
Conn_01x07,J2,PinHeader_1x11_P2.54mm_Vertical,,1
Conn_01x04,J5,PinHeader_2x02_P2.54mm_Vertical,,1
MountingHole,H2,MountingHole_2.2mm_M2,,1

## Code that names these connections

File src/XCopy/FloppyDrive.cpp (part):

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    registerSetup(1);
    pinMode(_dens, OUTPUT);
    digitalWriteFast(_dens, HIGH);
    pinMode(_index, INPUT_PULLUP);
    pinMode(_motor, OUTPUT);
    digitalWriteFast(_motor, HIGH);
    pinMode(_drivesel, OUTPUT);
    digitalWriteFast(_drivesel, HIGH);
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        driveSelect();
        digitalWriteFast(_motor, LOW);
        motor = true;
        delay(600); // more than plenty of time to spinup motor
        if (autoDensity)
            initDrive();
    }
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
    if (version == 1)
    {
        _dens = 14;      //2 density select IN
        _index = 15;     //8 index OUT
        _drivesel = 16;  //12 drive select 1 IN
        _motor = 17;     //16 motor1 on IN
        _dir = 18;       //18 direction IN
        _step = 19;      //20 step IN
        _writedata = 9;  //22 write data IN
        _writeen = 8;    //24 write enable IN
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    }
    else
    {
        _dens = 2;        //2 density select IN
        _index = 3;       //8 index OUT
        _drivesel = 4;    //12 drive select 1 IN
        _motor = 5;       //16 motor1 on IN
        _dir = 6;         //18 direction IN
        _step = 7;        //20 step IN
        _writedata = 8;   //22 write data IN
        _writeen = 9;     //24 write enable IN
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

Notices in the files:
src/XCopy/FloppyDrive.cpp:
partly based on DecodeSectorData and DecodeLongword from AFR.C, written by
Marco Veneri Copyright (C) 1997 released as public domain
